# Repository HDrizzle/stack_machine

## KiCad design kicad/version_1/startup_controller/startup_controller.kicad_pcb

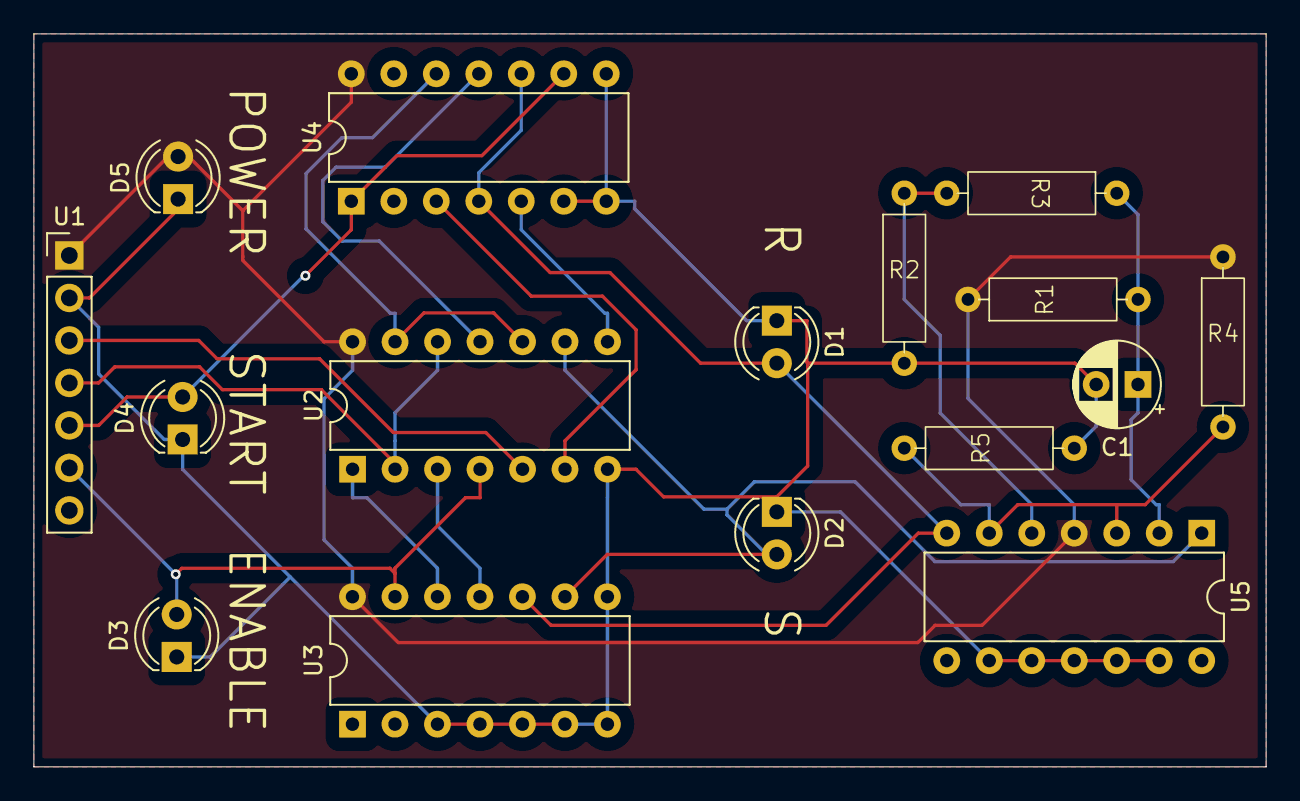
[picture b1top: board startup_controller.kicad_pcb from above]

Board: 2 copper layers, 73.7 x 43.8 mm, 16 parts (0 on the bottom side), 17 nets.

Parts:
C1: C; CP_Radial_D5.0mm_P2.50mm
D1, D2, D3, D4, D5: LED; LED_D4.0mm
R1, R2, R3, R4, R5: R; 0.4_pitch_resistor
U1: PinHeader_1x07_P2.54mm_Vertical
U2, U3, U4, U5: DIP-14_W7.62mm

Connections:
unnamed: D1.2 (A), U3.10 (1RESET), U4.4 (0RESET), U4.10 (1RESET), U5.7 (OUT_2)
unnamed: C1.2, D1.1 (K), D2.1 (K), D3.1 (K), D4.1 (K), D5.1 (K), R2.2, R5.2, U1.2 (GND), U2.7 (GND), U3.3 (0CLK), U3.4 (0RESET), U3.5 (0D), U3.6 (0SET), U3.7 (GND), U3.8 (1SET), U4.6 (0SET), U4.7 (GND), U4.8 (1SET), U5.9 (IN-_3), U5.10 (IN+_3), U5.11 (GND), U5.12 (IN+_4), U5.13 (IN-_4)
unnamed: D2.2 (A), U2.9 (4B), U3.9 (1D), U5.1 (OUT_1)
unnamed: D3.2 (A), U1.6 (ENABLE), U2.4 (2A), U3.13 (1Q)
unnamed: D4.2 (A), U1.5 (START), U4.1 (0Q), U4.9 (1D)
unnamed: D5.2 (A), R1.1, R4.1, U1.1 (V+), U2.14 (V+), U3.14 (V+), U4.14 (V+), U5.4 (V+)
unnamed: U1.3 (A_CLK), U2.5 (2B)
unnamed: U1.4 (B_CLK), U2.2 (1B), U2.12 (3B)
unnamed: U2.1 (1A), U3.12 (1Q3)
unnamed: U2.3 (1Q), U3.11 (1CLK)
unnamed: U2.6 (2Q), U4.3 (0CLK)
unnamed: U2.10 (4A), U2.13 (3A), U4.12 (1Q3)
unnamed: U2.11 (3Q), U4.11 (1CLK)
unnamed: U2.8 (4Q), U4.5 (0D)
unnamed: R4.2, R5.1, U5.3 (IN+_1), U5.6 (IN-_2)
unnamed: R2.1, R3.2, U5.5 (IN+_2)
unnamed: C1.1, R1.2, R3.1, U5.2 (IN-_1)

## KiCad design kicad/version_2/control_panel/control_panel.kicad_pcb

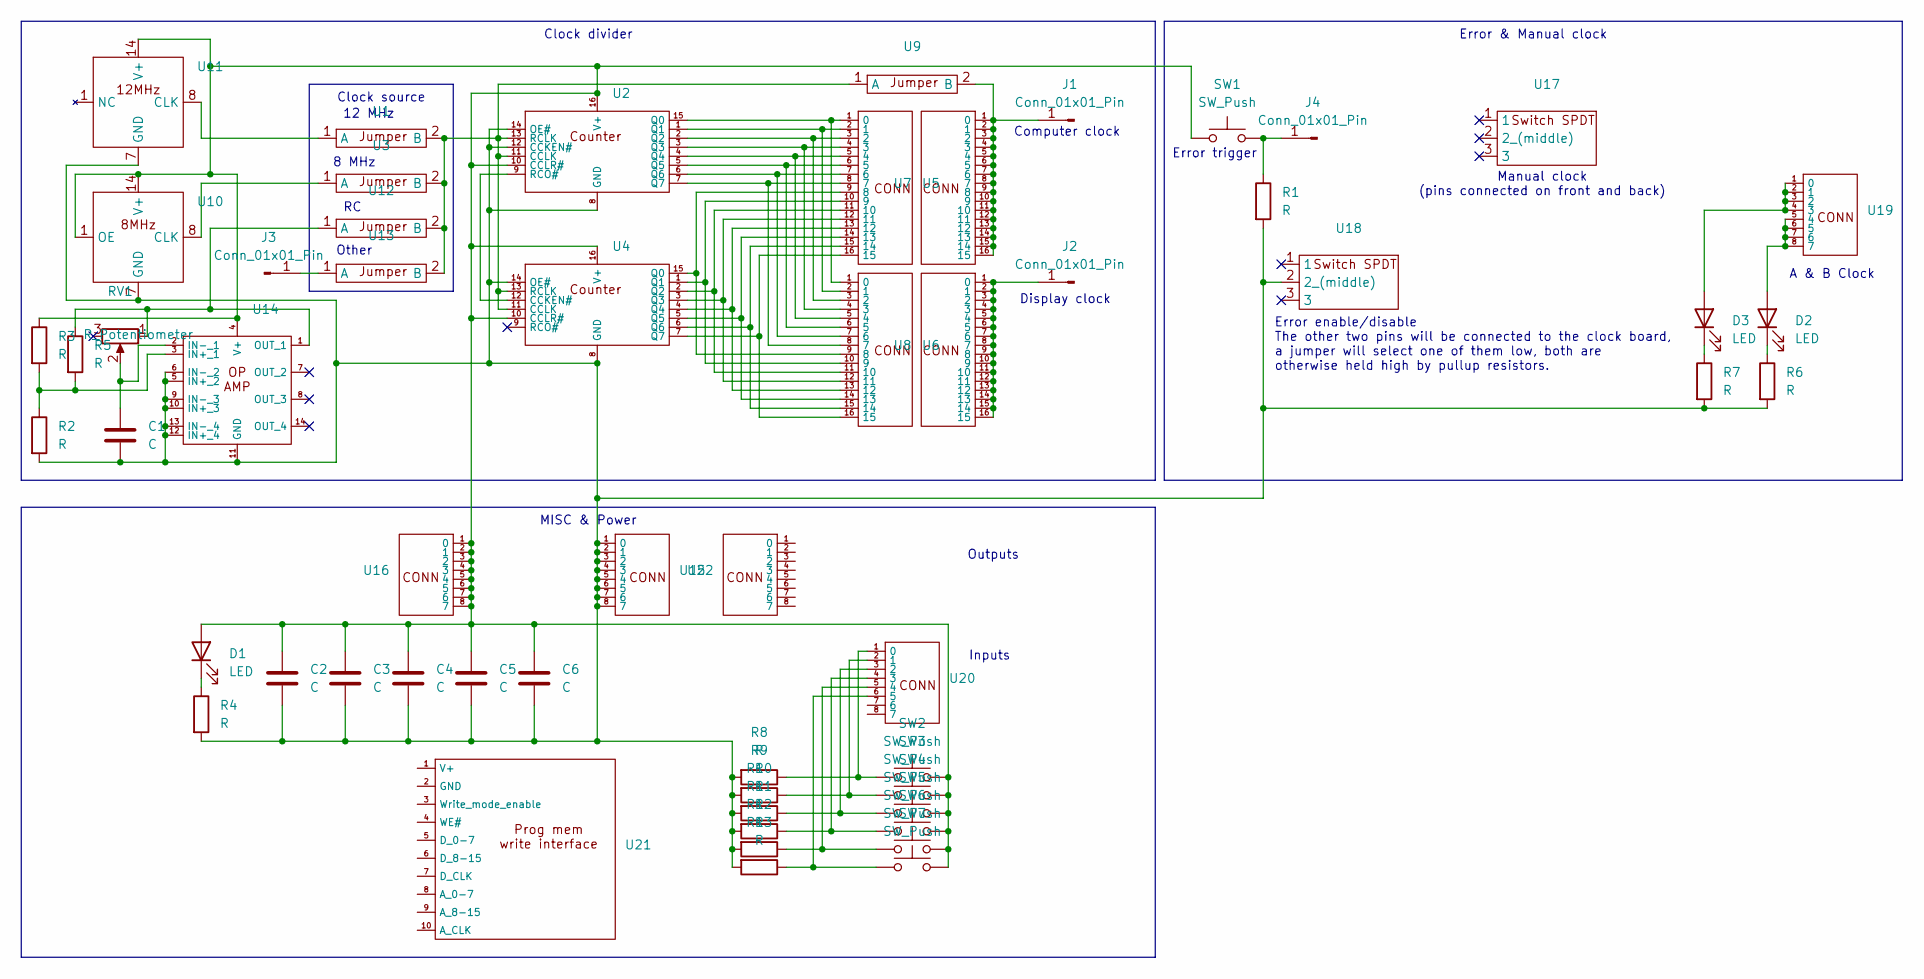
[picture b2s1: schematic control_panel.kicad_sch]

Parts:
C1: C; CP_Radial_D5.0mm_P2.50mm
C2, C3, C4, C5, C6: C; C_Rect_L11.0mm_W4.2mm_P10.00mm_MKT
D1, D2, D3: LED; LED_D3.0mm
J1, J2, J3, J4: Conn_01x01_Pin; PinHeader_1x01_P2.54mm_Vertical
R1, R2, R3, R4, R5, R6, R7, R8, R9, R10, R11, R12, R13: R; 0.4_pitch_resistor
RV1: R_Potentiometer; panel_mount_pot
SW1, SW2, SW3, SW4, SW5, SW6, SW7: SW_Push; SW_PUSH_6mm
U1, U3, U9, U12, U13: PinHeader_1x02_P2.54mm_Vertical
U2, U4: DIP-16_W7.62mm
U5, U6, U7, U8: PinHeader_1x16_P2.54mm_Vertical
U10, U11: crystal_dip_14
U14: DIP-14_W7.62mm
U15, U16, U19, U20, U22: PinHeader_1x08_P2.54mm_Vertical
U17: manual_clock_switch_side
U18: PinHeader_1x03_P2.54mm_Vertical
U21: PinHeader_1x10_P2.54mm_Horizontal

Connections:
unnamed: C2.1, C3.1, C4.1, C5.1, C6.1, D1.2 (A), R3.1, SW1.1, SW2.2, SW3.2, SW4.2, SW5.2, SW6.2, SW7.2, U2.10 (CCLR#), U2.16 (V+), U4.10 (CCLR#), U4.16 (V+), U10.1 (OE), U10.14 (V+), U11.14 (V+), U14.4 (V+), U16.1 (0), U16.2 (1), U16.3 (2), U16.4 (3), U16.5 (4), U16.6 (5), U16.7 (6), U16.8 (7)
unnamed: D1.1 (K), R4.1
unnamed: D2.2 (A), U19.5 (4), U19.6 (5), U19.7 (6), U19.8 (7)
unnamed: D2.1 (K), R6.1
unnamed: D3.2 (A), U19.1 (0), U19.2 (1), U19.3 (2), U19.4 (3)
unnamed: D3.1 (K), R7.1
unnamed: J1.1, U7.1 (0), U7.2 (1), U7.3 (2), U7.4 (3), U7.5 (4), U7.6 (5), U7.7 (6), U7.8 (7), U7.9 (8), U7.10 (9), U7.11 (10), U7.12 (11), U7.13 (12), U7.14 (13), U7.15 (14), U7.16 (15), U9.2 (B)
unnamed: J2.1, U8.1 (0), U8.2 (1), U8.3 (2), U8.4 (3), U8.5 (4), U8.6 (5), U8.7 (6), U8.8 (7), U8.9 (8), U8.10 (9), U8.11 (10), U8.12 (11), U8.13 (12), U8.14 (13), U8.15 (14), U8.16 (15)
unnamed: J3.1, U13.1 (A)
unnamed: J4.1, R1.1, SW1.2
unnamed: U1.1 (A), U11.8 (CLK)
unnamed: U1.2 (B), U2.11 (CCLK), U2.13 (RCLK), U3.2 (B), U4.11 (CCLK), U4.13 (RCLK), U9.1 (A), U12.2 (B), U13.2 (B)
unnamed: U2.15 (Q0), U5.1 (0), U6.1 (0)
unnamed: U2.1 (Q1), U5.2 (1), U6.2 (1)
unnamed: U2.2 (Q2), U5.3 (2), U6.3 (2)
unnamed: U2.3 (Q3), U5.4 (3), U6.4 (3)
unnamed: U2.4 (Q4), U5.5 (4), U6.5 (4)
unnamed: U2.5 (Q5), U5.6 (5), U6.6 (5)
unnamed: U2.6 (Q6), U5.7 (6), U6.7 (6)
unnamed: U2.7 (Q7), U5.8 (7), U6.8 (7)
unnamed: U2.9 (RCO#), U4.12 (CCKEN#)
unnamed: U4.15 (Q0), U5.9 (8), U6.9 (8)
unnamed: U4.1 (Q1), U5.10 (9), U6.10 (9)
unnamed: U4.2 (Q2), U5.11 (10), U6.11 (10)
unnamed: U4.3 (Q3), U5.12 (11), U6.12 (11)
unnamed: U4.4 (Q4), U5.13 (12), U6.13 (12)
unnamed: U4.5 (Q5), U5.14 (13), U6.14 (13)
unnamed: U4.6 (Q6), U5.15 (14), U6.15 (14)
unnamed: U4.7 (Q7), U5.16 (15), U6.16 (15)
unnamed: U3.1 (A), U10.8 (CLK)
unnamed: C1.2, C2.2, C3.2, C4.2, C5.2, C6.2, R1.2, R2.2, R4.2, R6.2, R7.2, R8.2, R9.2, R10.2, R11.2, R12.2, R13.2, U2.8 (GND), U2.12 (CCKEN#), U2.14 (OE#), U4.8 (GND), U4.14 (OE#), U10.7 (GND), U11.7 (GND), U14.5 (IN+_2), U14.6 (IN-_2), U14.9 (IN-_3), U14.10 (IN+_3), U14.11 (GND), U14.12 (IN+_4), U14.13 (IN-_4), U15.1 (0), U15.2 (1), U15.3 (2), U15.4 (3), U15.5 (4), U15.6 (5), U15.7 (6), U15.8 (7), U18.2 (2_(middle))
unnamed: R5.1, RV1.1, U12.1 (A), U14.1 (OUT_1)
unnamed: R2.1, R3.2, R5.2, U14.3 (IN+_1)
unnamed: C1.1, RV1.2, U14.2 (IN-_1)
unnamed: R8.1, SW2.1, U20.1 (0)
unnamed: R9.1, SW3.1, U20.2 (1)
unnamed: R10.1, SW4.1, U20.3 (2)
unnamed: R11.1, SW5.1, U20.4 (3)
unnamed: R12.1, SW6.1, U20.5 (4)
unnamed: R13.1, SW7.1, U20.6 (5)

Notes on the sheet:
Error & Manual clock
MISC & Power
Clock divider
Clock source
Outputs
12 MHz
Error enable/disable The other two pins will be connected to the clock board, a jumper will select one of them low, both are otherwise held high by pullup resistors.
Other
Display clock
Computer clock
8 MHz
Manual clock (pins connected on front and back)
Error trigger
Inputs
A & B Clock

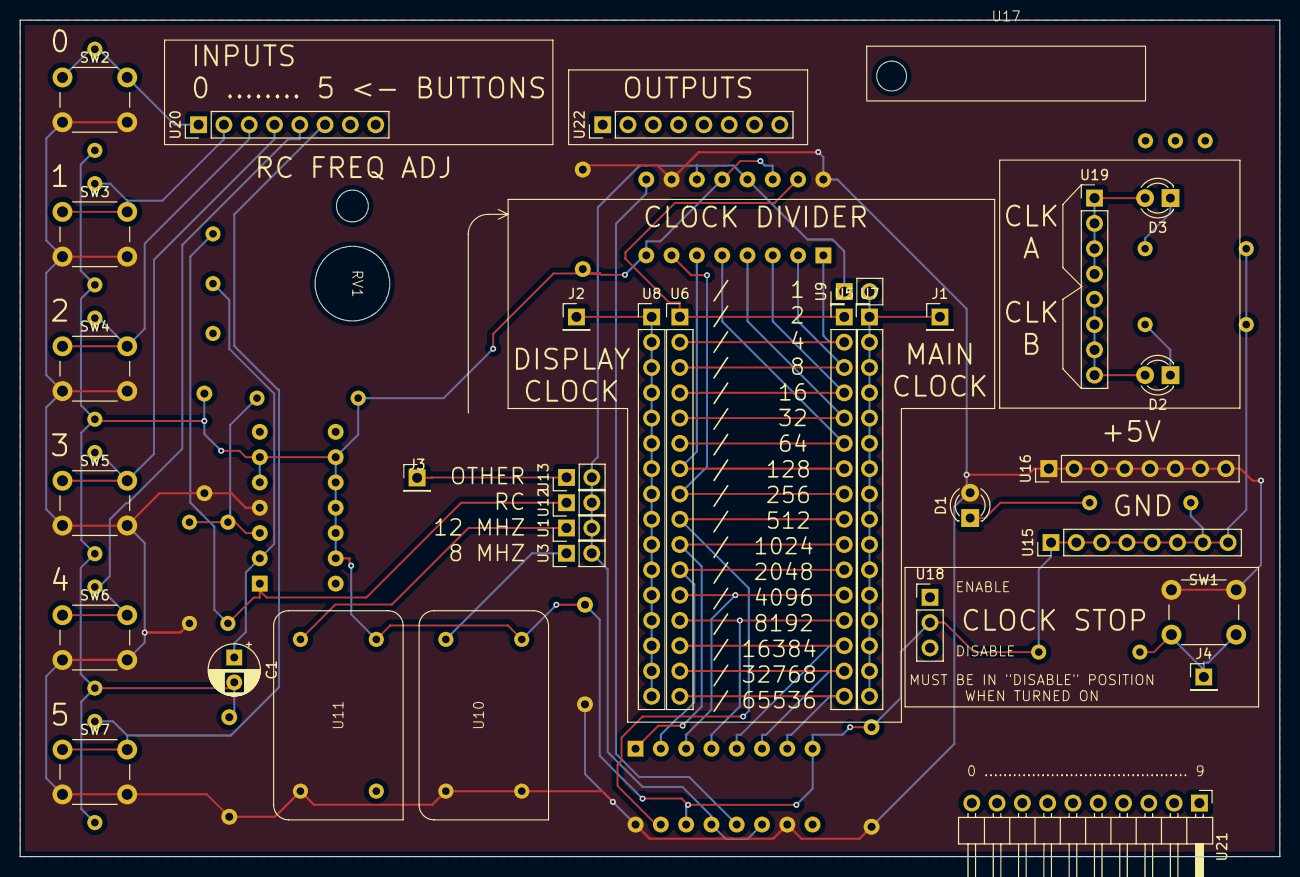
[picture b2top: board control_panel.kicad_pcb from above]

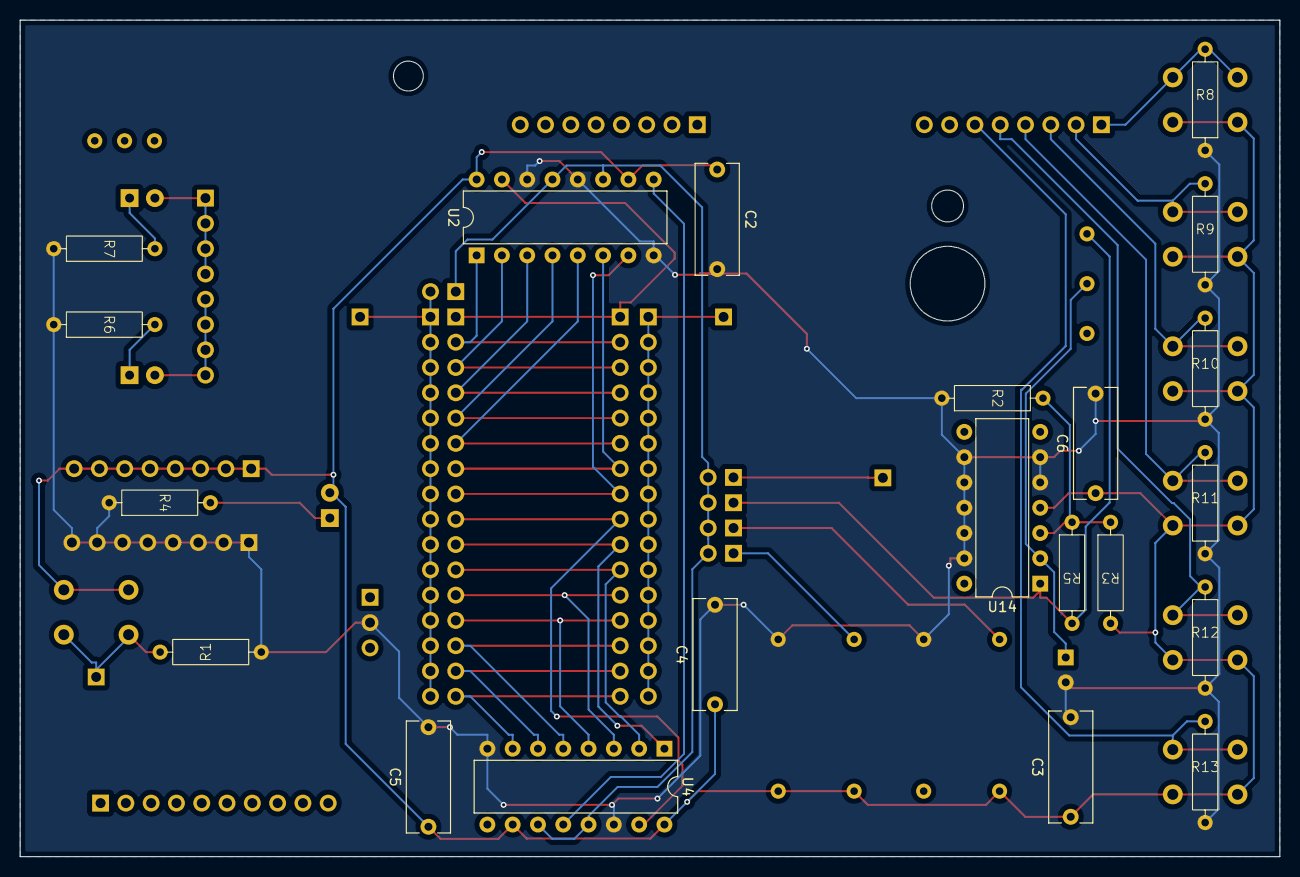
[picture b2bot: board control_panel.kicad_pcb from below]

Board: 2 copper layers, 126.5 x 84.0 mm, 56 parts (21 on the bottom side), 40 nets.

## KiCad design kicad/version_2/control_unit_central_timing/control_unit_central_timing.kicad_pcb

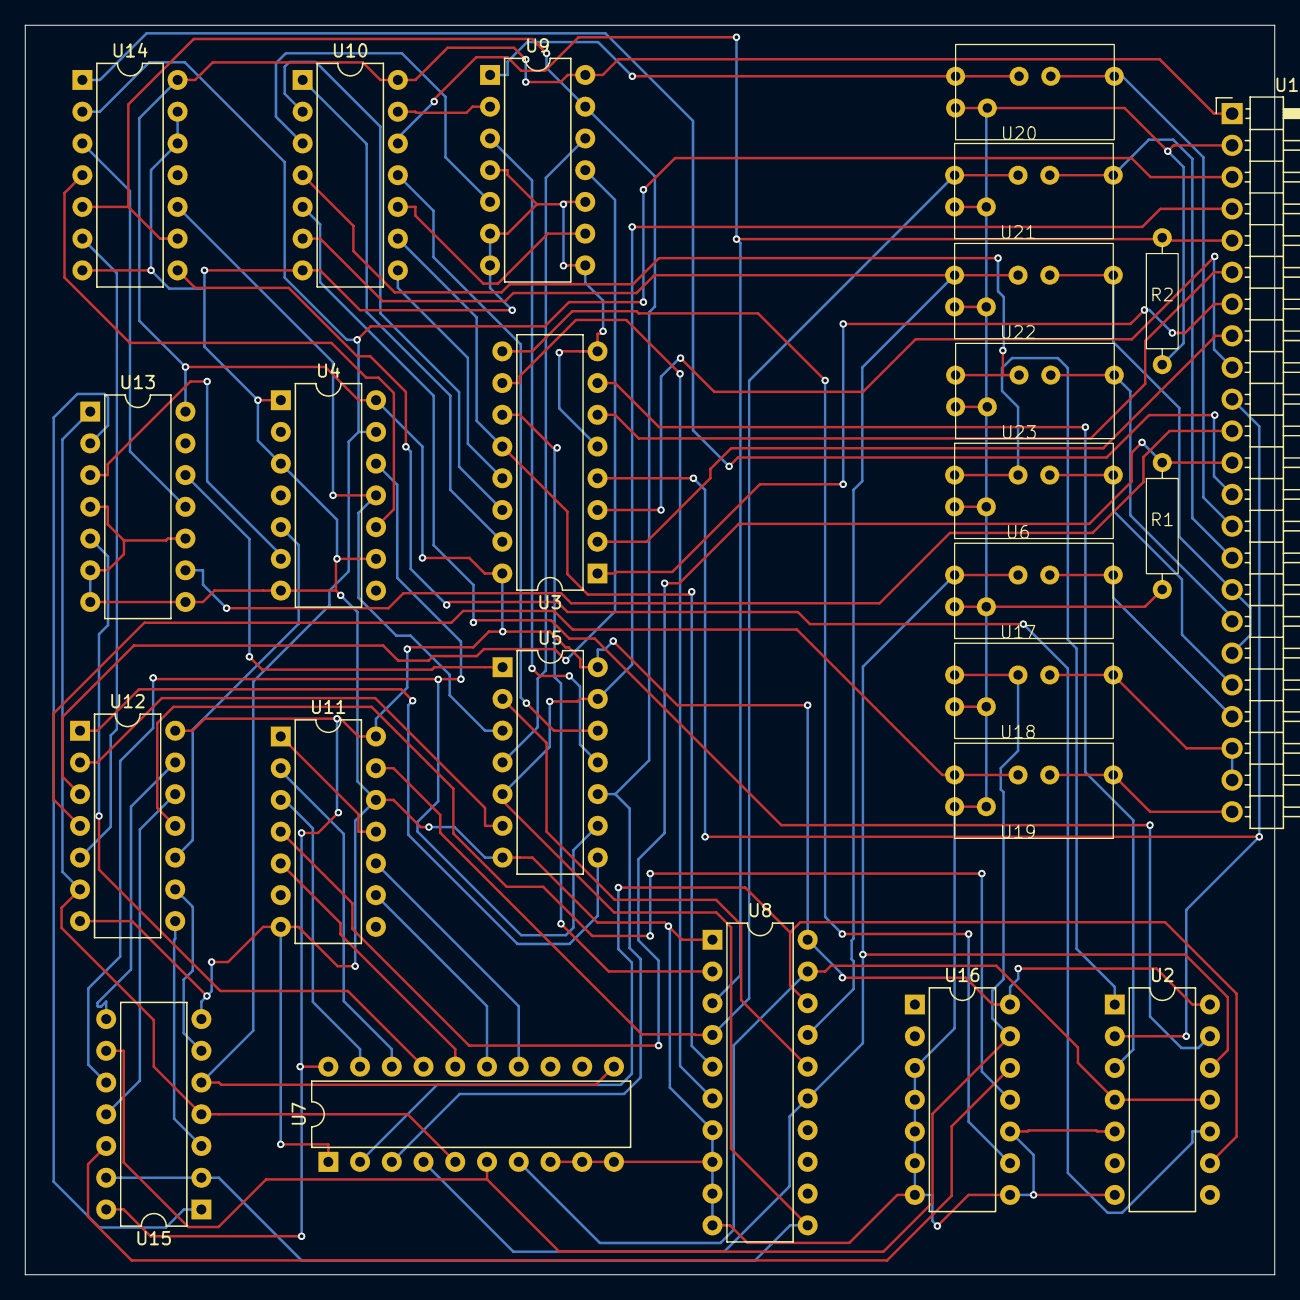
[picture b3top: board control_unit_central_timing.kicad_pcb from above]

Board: 2 copper layers, 100.0 x 100.0 mm, 25 parts (0 on the bottom side), 75 nets.

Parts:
R1, R2: 10k; 0.4_pitch_resistor
U1: PinHeader_1x23_P2.54mm_Horizontal
U2, U4, U5, U9, U10, U11, U12, U13, U14, U15, U16: DIP-14_W7.62mm
U3: DIP-16_W7.62mm
U6, U17, U18, U19, U20, U21, U22, U23: jumper
U7, U8: DIP-20_W7.62mm

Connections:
unnamed: U1.3 (A_CLK), U4.13 (I5), U7.11 (CLK), U14.2 (1B), U15.5 (2B)
unnamed: U1.11 (BUS-0), U13.9 (1D)
unnamed: U1.14 (BUS_MOVE), U20.3 (OUT)
unnamed: R2.1, U1.5 (BUS_MOVE_DONE), U8.3 (D1), U10.12 (3A)
unnamed: U1.13 (BUS_READ_GOTO-DECIDER), U14.1 (1A)
unnamed: U1.4 (B_CLK), U5.5 (2B), U5.13 (3A), U8.11 (CLK), U15.2 (1B), U15.13 (3A)
unnamed: U1.21 (CALL_STACK-POP), U1.22 (CALL_STACK-OE), U18.3 (OUT)
unnamed: U1.20 (CALL_STACK-PUSH), U17.3 (OUT)
unnamed: U1.19 (FAULT), U6.3 (OUT)
unnamed: R1.2, R2.2, U1.2 (GND), U2.5 (A3), U2.7 (GND), U3.5 (E3#), U3.8 (GND), U4.1 (I0), U4.3 (I1), U4.7 (GND), U4.9 (I3), U5.7 (GND), U6.2 (GND), U7.1 (OE#), U7.8 (D6), U7.9 (D7), U7.10 (GND), U8.1 (OE#), U8.7 (D5), U8.8 (D6), U8.9 (D7), U8.10 (GND), U9.4 (0RESET), U9.6 (0SET), U9.7 (GND), U9.8 (1SET), U9.10 (1RESET), U10.7 (GND), U11.7 (GND), U11.12 (B3), U12.7 (GND), U13.4 (0RESET), U13.6 (0SET), U13.7 (GND), U13.8 (1SET), U13.10 (1RESET), U14.7 (GND), U14.12 (3B), U14.13 (3A), U15.7 (GND), U16.3 (0CLK), U16.4 (0RESET), U16.5 (0D), U16.6 (0SET), U16.7 (GND), U16.8 (1SET), U16.10 (1RESET), U17.2 (GND), U18.2 (GND), U19.2 (GND), U20.2 (GND), U21.2 (GND), U22.2 (GND), U23.2 (GND)
unnamed: U1.23 (GOTO_LATCHES_OE), U19.3 (OUT)
unnamed: U1.7 (INSTRUCTION-0), U3.1 (A0)
unnamed: U1.8 (INSTRUCTION-1), U3.2 (A1)
unnamed: U1.9 (INSTRUCTION-2), U3.3 (A2)
unnamed: U1.10 (INSTRUCTION-3), U2.2 (A0), U3.4 (E2#)
unnamed: U1.16 (POST_ADDER_LATCH_CLOCK), U1.18 (PROG_READ), U22.3 (OUT)
unnamed: U1.17 (POST_ADDER_LATCH_OE), U23.3 (OUT)
unnamed: U1.15 (PRE_ADDER_LATCH_CLOCK), U21.3 (OUT)
unnamed: U1.6 (PROG_READ_DONE), U3.6 (E1)
unnamed: R1.1, U1.12 (START), U11.4 (A2)
unnamed: U1.1 (V+), U2.14 (V+), U3.16 (V+), U4.14 (V+), U5.14 (V+), U7.20 (V+), U8.20 (V+), U9.14 (V+), U10.14 (V+), U11.14 (V+), U12.14 (V+), U13.14 (V+), U14.14 (V+), U15.14 (V+), U16.14 (V+)
unnamed: U2.3 (A1), U3.7 (Y7)
unnamed: U2.4 (A2), U2.11 (B2), U7.7 (D5), U8.19 (Q0)
unnamed: U2.9 (B0), U7.2 (D0), U8.18 (Q1)
unnamed: U2.1 (OA), U6.1 (IN)
unnamed: U3.11 (Y4), U8.2 (D0)
unnamed: U3.10 (Y5), U8.6 (D4)
unnamed: U5.2 (1B), U8.16 (Q3)
unnamed: U5.4 (2A), U9.12 (1Q3)
unnamed: U5.11 (3Q), U9.3 (0CLK)
unnamed: U3.15 (Y0), U10.1 (0A)
unnamed: U3.14 (Y1), U10.2 (0B)
unnamed: U2.13 (OB), U10.5 (1A)
unnamed: U8.17 (Q2), U10.6 (1B), U22.1 (IN)
unnamed: U3.13 (Y2), U10.8 (2A)
unnamed: U3.12 (Y3), U8.5 (D3), U10.9 (2B)
unnamed: U9.2 (0Q#), U10.13 (3B)
unnamed: U9.5 (0D), U10.3 (Q0)
unnamed: U10.4 (Q1), U23.1 (IN)
unnamed: U9.9 (1D), U10.10 (Q2)
unnamed: U5.12 (3B), U10.11 (Q3)
unnamed: U7.18 (Q1), U11.2 (A0)
unnamed: U7.19 (Q0), U11.3 (A1)
unnamed: U7.16 (Q3), U11.5 (A3)
unnamed: U7.15 (Q4), U11.9 (B0)
unnamed: U7.14 (Q5), U11.10 (B1)
unnamed: U11.1 (OA), U11.11 (B2)
unnamed: U8.4 (D2), U11.13 (OB), U21.1 (IN)
unnamed: U5.8 (4Q), U12.1 (0A)
unnamed: U5.6 (2Q), U12.2 (0B)
unnamed: U12.5 (1A), U14.6 (2Q)
unnamed: U7.5 (D3), U12.6 (1B), U13.1 (0Q), U15.4 (2A)
unnamed: U12.8 (2A), U15.3 (1Q)
unnamed: U12.9 (2B), U15.6 (2Q)
unnamed: U12.12 (3A), U15.11 (3Q)
unnamed: U12.13 (3B), U15.8 (4Q)
unnamed: U9.11 (1CLK), U12.3 (Q0)
unnamed: U12.4 (Q1), U19.1 (IN)
unnamed: U4.5 (I2), U12.10 (Q2)
unnamed: U12.11 (Q3), U16.11 (1CLK)
unnamed: U4.6 (O2), U13.3 (0CLK)
unnamed: U7.17 (Q2), U13.5 (0D)
unnamed: U13.2 (0Q#), U15.1 (1A)
unnamed: U13.11 (1CLK), U14.3 (1Q)
unnamed: U5.1 (1A), U13.12 (1Q3)
unnamed: U4.10 (O4), U14.4 (2A)
unnamed: U5.10 (4A), U7.3 (D1), U9.13 (1Q), U14.5 (2B), U14.9 (4B)
unnamed: U4.11 (I4), U5.3 (1Q), U14.10 (4A)
unnamed: U2.10 (B1), U14.8 (4Q)
unnamed: U15.12 (3B), U16.12 (1Q3)
unnamed: U4.12 (O5), U5.9 (4B), U15.10 (4A)
unnamed: U7.6 (D4), U15.9 (4B), U16.13 (1Q), U18.1 (IN)
unnamed: U3.9 (Y6), U16.9 (1D)
unnamed: U2.12 (B3), U7.4 (D2), U8.15 (Q4), U17.1 (IN)
unnamed: U9.1 (0Q), U20.1 (IN)

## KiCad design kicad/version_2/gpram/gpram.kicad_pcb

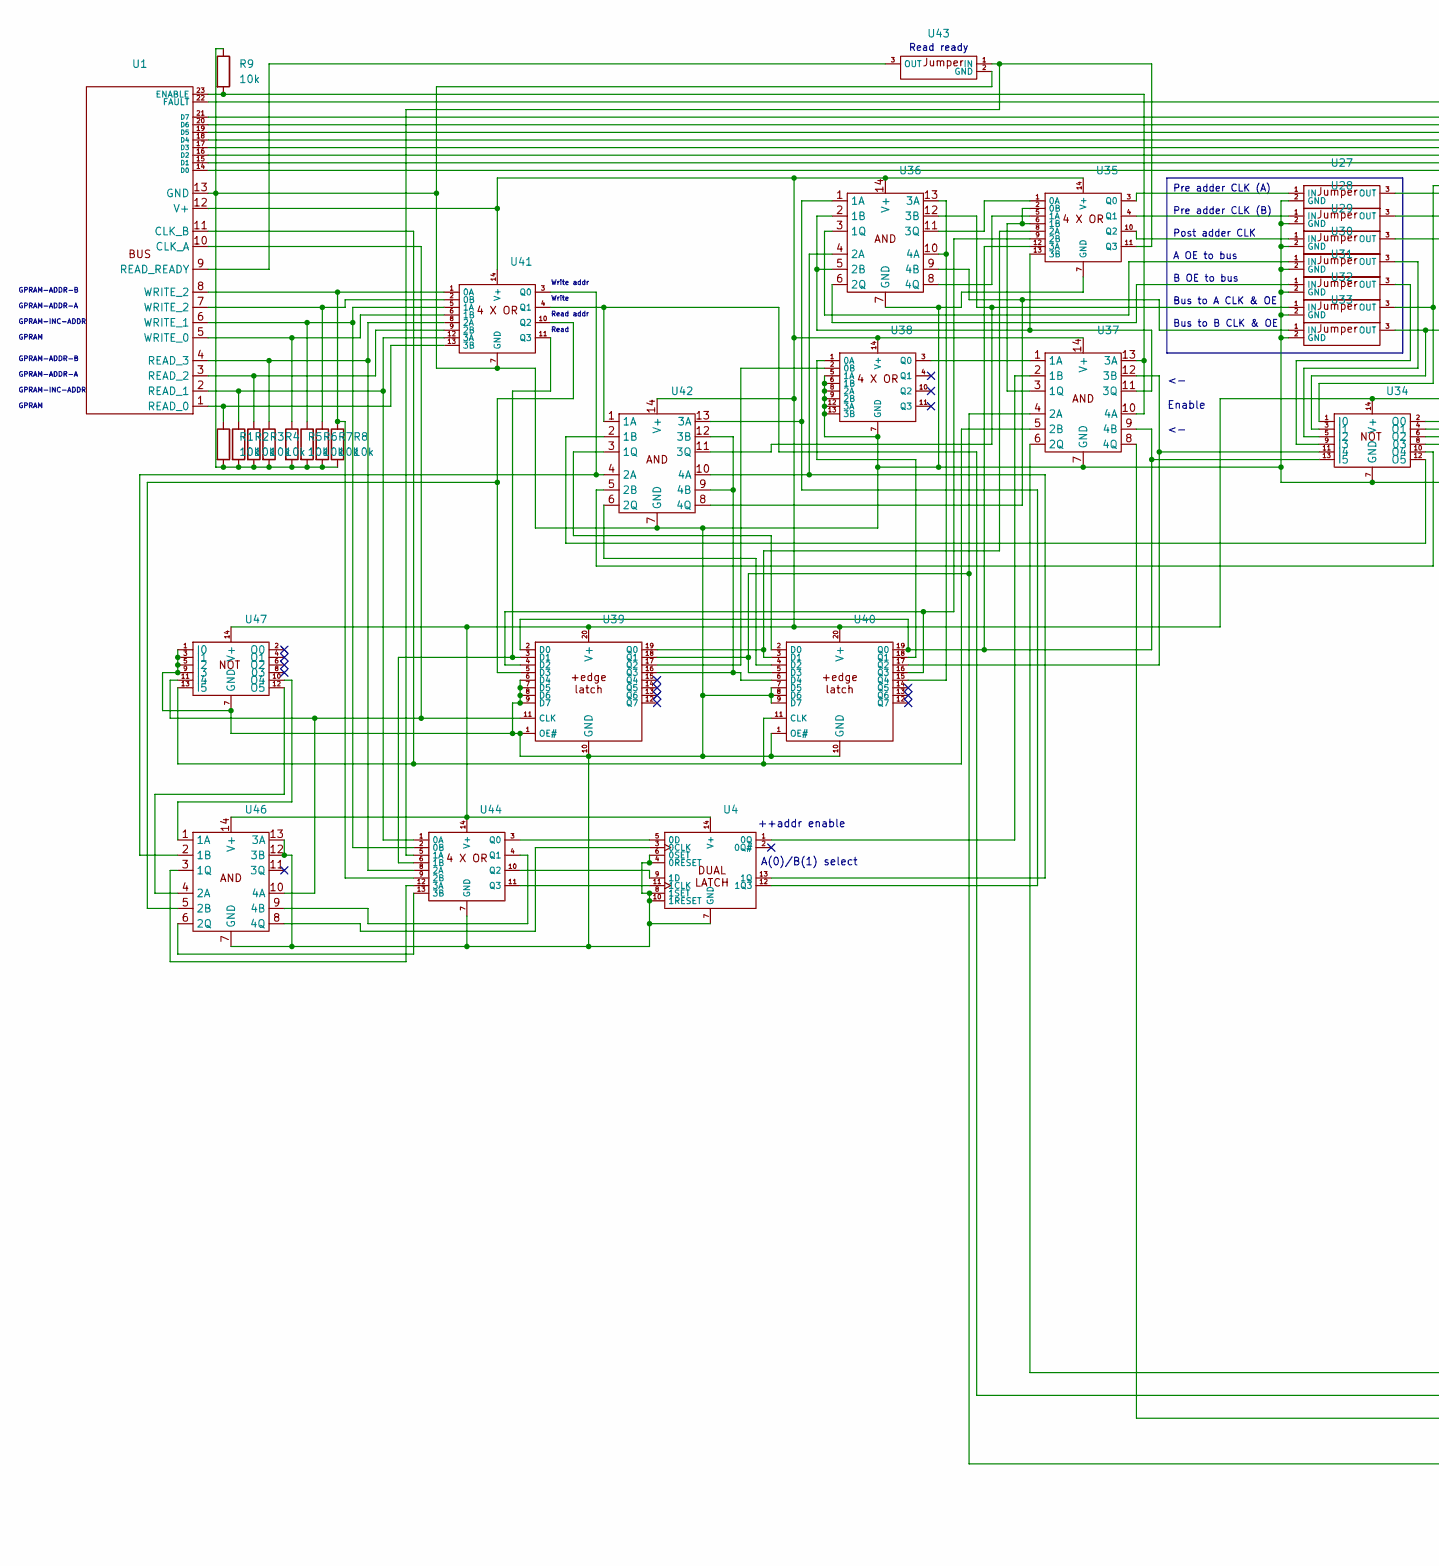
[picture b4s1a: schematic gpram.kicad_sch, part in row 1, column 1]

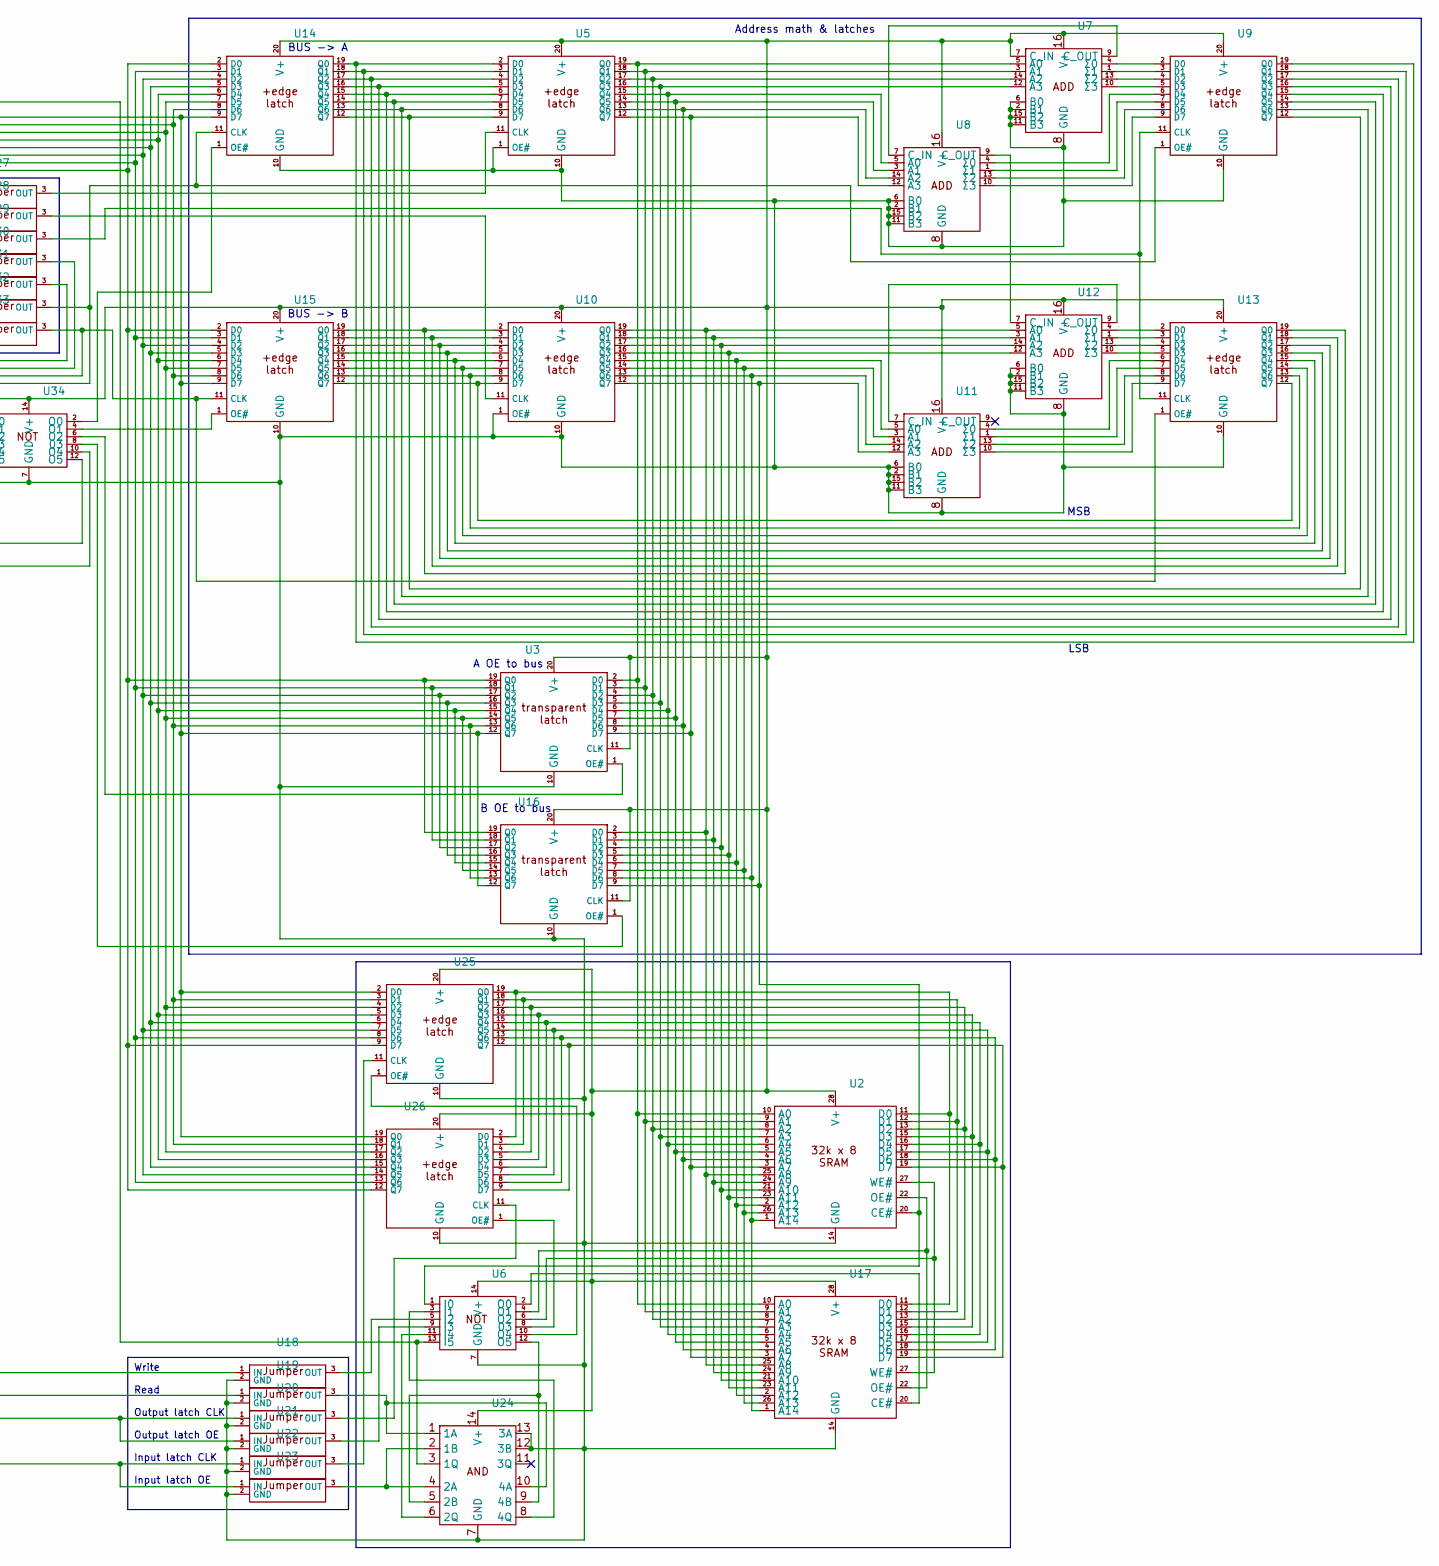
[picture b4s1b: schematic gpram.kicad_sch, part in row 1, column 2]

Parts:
R1, R2, R3, R4, R5, R6, R7, R8, R9: 10k; 0.4_pitch_resistor
U1: PinHeader_1x23_P2.54mm_Vertical
U2, U17: DIP-28_W15.24mm
U3, U5, U9, U10, U13, U14, U15, U16, U25, U26, U39, U40: DIP-20_W7.62mm
U4, U6, U24, U34, U35, U36, U37, U38, U41, U42, U44, U46, U47: DIP-14_W7.62mm
U7, U8, U11, U12: DIP-16_W7.62mm
U18, U19, U20, U21, U22, U23, U27, U28, U29, U30, U31, U32, U33, U43: jumper

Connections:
unnamed: U1.10 (CLK_A), U39.11 (CLK), U46.10 (4A), U47.11 (I4)
unnamed: U1.11 (CLK_B), U37.5 (2B), U40.11 (CLK), U47.13 (I5)
unnamed: U1.14 (D0), U3.19 (Q0), U14.2 (D0), U15.2 (D0), U16.19 (Q0), U25.9 (D7), U26.12 (Q7)
unnamed: U1.15 (D1), U3.18 (Q1), U14.3 (D1), U15.3 (D1), U16.18 (Q1), U25.8 (D6), U26.13 (Q6)
unnamed: U1.16 (D2), U3.17 (Q2), U14.4 (D2), U15.4 (D2), U16.17 (Q2), U25.7 (D5), U26.14 (Q5)
unnamed: U1.17 (D3), U3.16 (Q3), U14.5 (D3), U15.5 (D3), U16.16 (Q3), U25.6 (D4), U26.15 (Q4)
unnamed: U1.18 (D4), U3.15 (Q4), U14.6 (D4), U15.6 (D4), U16.15 (Q4), U25.5 (D3), U26.16 (Q3)
unnamed: U1.19 (D5), U3.14 (Q5), U14.7 (D5), U15.7 (D5), U16.14 (Q5), U25.4 (D2), U26.17 (Q2)
unnamed: U1.20 (D6), U3.13 (Q6), U14.8 (D6), U15.8 (D6), U16.13 (Q6), U25.3 (D1), U26.18 (Q1)
unnamed: U1.21 (D7), U3.12 (Q7), U14.9 (D7), U15.9 (D7), U16.12 (Q7), U25.2 (D0), U26.19 (Q0)
unnamed: R9.2, U1.23 (ENABLE), U37.10 (4A), U37.13 (3A)
unnamed: U1.22 (FAULT), U6.13 (I5), U24.3 (1Q)
unnamed: R1.2, R2.2, R3.2, R4.2, R5.2, R6.2, R7.2, R8.2, R9.1, U1.13 (GND), U2.14 (GND), U3.10 (GND), U4.4 (0RESET), U4.6 (0SET), U4.7 (GND), U4.8 (1SET), U4.10 (1RESET), U5.1 (OE#), U5.10 (GND), U6.7 (GND), U7.2 (B1), U7.6 (B0), U7.8 (GND), U7.11 (B3), U7.15 (B2), U8.2 (B1), U8.6 (B0), U8.8 (GND), U8.11 (B3), U8.15 (B2), U9.10 (GND), U10.1 (OE#), U10.10 (GND), U11.2 (B1), U11.6 (B0), U11.8 (GND), U11.11 (B3), U11.15 (B2), U12.2 (B1), U12.6 (B0), U12.8 (GND), U12.11 (B3), U12.15 (B2), U13.10 (GND), U14.10 (GND), U15.10 (GND), U16.10 (GND), U17.14 (GND), U18.2 (GND), U19.2 (GND), U20.2 (GND), U21.2 (GND), U22.2 (GND), U23.2 (GND), U24.7 (GND), U24.12 (3B), U24.13 (3A), U25.10 (GND), U26.10 (GND), U27.2 (GND), U28.2 (GND), U29.2 (GND), U30.2 (GND), U31.2 (GND), U32.2 (GND), U33.2 (GND), U34.7 (GND), U35.7 (GND), U36.7 (GND), U37.7 (GND), U38.5 (1A), U38.6 (1B), U38.7 (GND), U38.8 (2A), U38.9 (2B), U38.12 (3A), U38.13 (3B), U39.1 (OE#), U39.6 (D4), U39.7 (D5), U39.8 (D6), U39.9 (D7), U39.10 (GND), U40.1 (OE#), U40.7 (D5), U40.8 (D6), U40.9 (D7), U40.10 (GND), U41.7 (GND), U42.7 (GND), U43.2 (GND), U44.7 (GND), U46.7 (GND), U46.12 (3B), U46.13 (3A), U47.1 (I0), U47.3 (I1), U47.5 (I2), U47.7 (GND), U47.9 (I3)
unnamed: R1.1, U1.1 (READ_0), U41.13 (3B)
unnamed: R2.1, U1.2 (READ_1), U41.12 (3A), U44.1 (0A)
unnamed: R3.1, U1.3 (READ_2), U41.9 (2B)
unnamed: R4.1, U1.4 (READ_3), U41.8 (2A), U44.8 (2A)
unnamed: U1.9 (READ_READY), U43.3 (OUT)
unnamed: U1.12 (V+), U2.28 (V+), U3.11 (CLK), U3.20 (V+), U4.14 (V+), U5.20 (V+), U6.14 (V+), U7.7 (C_IN), U7.16 (V+), U8.16 (V+), U9.20 (V+), U10.20 (V+), U11.16 (V+), U12.16 (V+), U13.20 (V+), U14.20 (V+), U15.20 (V+), U16.11 (CLK), U16.20 (V+), U17.28 (V+), U24.14 (V+), U25.20 (V+), U26.20 (V+), U34.14 (V+), U35.14 (V+), U36.14 (V+), U37.14 (V+), U38.14 (V+), U39.20 (V+), U40.20 (V+), U41.14 (V+), U42.14 (V+), U44.14 (V+), U46.14 (V+), U47.14 (V+)
unnamed: R5.1, U1.5 (WRITE_0), U41.6 (1B)
unnamed: R6.1, U1.6 (WRITE_1), U41.5 (1A), U44.2 (0B)
unnamed: U3.1 (OE#), U34.6 (O2)
unnamed: U4.3 (0CLK), U46.8 (4Q)
unnamed: U4.5 (0D), U44.3 (Q0)
unnamed: U4.11 (1CLK), U44.11 (Q3)
unnamed: U4.9 (1D), U44.10 (Q2)
unnamed: U7.9 (C_OUT), U8.7 (C_IN)
unnamed: U7.4 (Σ0), U9.2 (D0)
unnamed: U7.1 (Σ1), U9.3 (D1)
unnamed: U7.13 (Σ2), U9.4 (D2)
unnamed: U7.10 (Σ3), U9.5 (D3)
unnamed: U8.4 (Σ0), U9.6 (D4)
unnamed: U8.1 (Σ1), U9.7 (D5)
unnamed: U8.13 (Σ2), U9.8 (D6)
unnamed: U8.10 (Σ3), U9.9 (D7)
unnamed: U10.11 (CLK), U28.3 (OUT)
unnamed: U10.2 (D0), U13.19 (Q0), U15.19 (Q0)
unnamed: U10.3 (D1), U13.18 (Q1), U15.18 (Q1)
unnamed: U10.4 (D2), U13.17 (Q2), U15.17 (Q2)
unnamed: U10.5 (D3), U13.16 (Q3), U15.16 (Q3)
unnamed: U10.6 (D4), U13.15 (Q4), U15.15 (Q4)
unnamed: U10.7 (D5), U13.14 (Q5), U15.14 (Q5)
unnamed: U10.8 (D6), U13.13 (Q6), U15.13 (Q6)
unnamed: U10.9 (D7), U13.12 (Q7), U15.12 (Q7)
unnamed: U2.25 (A8), U10.19 (Q0), U12.5 (A0), U16.2 (D0), U17.25 (A8)
unnamed: U2.24 (A9), U10.18 (Q1), U12.3 (A1), U16.3 (D1), U17.24 (A9)
unnamed: U2.21 (A10), U10.17 (Q2), U12.14 (A2), U16.4 (D2), U17.21 (A10)
unnamed: U2.23 (A11), U10.16 (Q3), U12.12 (A3), U16.5 (D3), U17.23 (A11)
unnamed: U2.2 (A12), U10.15 (Q4), U11.5 (A0), U16.6 (D4), U17.2 (A12)
unnamed: U2.26 (A13), U10.14 (Q5), U11.3 (A1), U16.7 (D5), U17.26 (A13)
unnamed: U2.1 (A14), U10.13 (Q6), U11.14 (A2), U16.8 (D6), U17.1 (A14)
unnamed: U2.20 (CE#), U6.1 (I0), U10.12 (Q7), U11.12 (A3), U16.9 (D7)
unnamed: U11.7 (C_IN), U12.9 (C_OUT)
unnamed: U11.4 (Σ0), U13.6 (D4)
unnamed: U11.1 (Σ1), U13.7 (D5)
unnamed: U11.13 (Σ2), U13.8 (D6)
unnamed: U11.10 (Σ3), U13.9 (D7)
unnamed: U8.9 (C_OUT), U12.7 (C_IN)
unnamed: U12.4 (Σ0), U13.2 (D0)
unnamed: U12.1 (Σ1), U13.3 (D1)
unnamed: U12.13 (Σ2), U13.4 (D2)
unnamed: U12.10 (Σ3), U13.5 (D3)
unnamed: U9.11 (CLK), U13.11 (CLK), U29.3 (OUT)
unnamed: U13.1 (OE#), U15.11 (CLK), U33.3 (OUT), U34.3 (I1)
unnamed: U9.1 (OE#), U14.11 (CLK), U32.3 (OUT), U34.1 (I0)
unnamed: U14.1 (OE#), U34.2 (O0)
unnamed: U5.2 (D0), U9.19 (Q0), U14.19 (Q0)
unnamed: U5.3 (D1), U9.18 (Q1), U14.18 (Q1)
unnamed: U5.4 (D2), U9.17 (Q2), U14.17 (Q2)
unnamed: U5.5 (D3), U9.16 (Q3), U14.16 (Q3)
unnamed: U5.6 (D4), U9.15 (Q4), U14.15 (Q4)
unnamed: U5.7 (D5), U9.14 (Q5), U14.14 (Q5)
unnamed: U5.8 (D6), U9.13 (Q6), U14.13 (Q6)
unnamed: U5.9 (D7), U9.12 (Q7), U14.12 (Q7)
unnamed: U15.1 (OE#), U34.4 (O1)
unnamed: U16.1 (OE#), U34.8 (03)
unnamed: U2.10 (A0), U3.2 (D0), U5.19 (Q0), U7.5 (A0), U17.10 (A0)
unnamed: U2.9 (A1), U3.3 (D1), U5.18 (Q1), U7.3 (A1), U17.9 (A1)
unnamed: U2.8 (A2), U3.4 (D2), U5.17 (Q2), U7.14 (A2), U17.8 (A2)
unnamed: U2.7 (A3), U3.5 (D3), U5.16 (Q3), U7.12 (A3), U17.7 (A3)
unnamed: U2.6 (A4), U3.6 (D4), U5.15 (Q4), U8.5 (A0), U17.6 (A4)
unnamed: U2.5 (A5), U3.7 (D5), U5.14 (Q5), U8.3 (A1), U17.5 (A5)
unnamed: U2.4 (A6), U3.8 (D6), U5.13 (Q6), U8.14 (A2), U17.4 (A6)
unnamed: U2.3 (A7), U3.9 (D7), U5.12 (Q7), U8.12 (A3), U17.3 (A7)
unnamed: U6.2 (O0), U17.20 (CE#)
unnamed: U2.11 (D0), U17.11 (D0), U25.19 (Q0), U26.2 (D0)
unnamed: U2.12 (D1), U17.12 (D1), U25.18 (Q1), U26.3 (D1)
unnamed: U2.13 (D2), U17.13 (D2), U25.17 (Q2), U26.4 (D2)
unnamed: U2.15 (D3), U17.15 (D3), U25.16 (Q3), U26.5 (D3)
unnamed: U2.16 (D4), U17.16 (D4), U25.15 (Q4), U26.6 (D4)
unnamed: U2.17 (D5), U17.17 (D5), U25.14 (Q5), U26.7 (D5)
unnamed: U2.18 (D6), U17.18 (D6), U25.13 (Q6), U26.8 (D6)
unnamed: U2.19 (D7), U17.19 (D7), U25.12 (Q7), U26.9 (D7)
unnamed: U2.22 (OE#), U6.4 (O1), U17.22 (OE#)
unnamed: U2.27 (WE#), U6.6 (O2), U17.27 (WE#)
unnamed: U18.1 (IN), U37.6 (2Q)
unnamed: U6.5 (I2), U18.3 (OUT)
unnamed: U19.1 (IN), U41.4 (Q1), U42.1 (1A)
unnamed: U19.3 (OUT), U24.1 (1A), U24.10 (4A)
unnamed: U20.1 (IN), U21.1 (IN), U37.8 (4Q)
unnamed: U20.3 (OUT), U26.11 (CLK)
unnamed: U6.9 (I3), U21.3 (OUT)
unnamed: U22.1 (IN), U23.1 (IN), U37.4 (2A), U39.18 (Q1), U40.5 (D3)
unnamed: U22.3 (OUT), U25.11 (CLK)
unnamed: U23.3 (OUT), U24.2 (1B), U24.4 (2A)
unnamed: U6.12 (O5), U24.5 (2B), U24.9 (4B)
unnamed: U6.11 (I4), U24.6 (2Q)
unnamed: U6.3 (I1), U24.8 (4Q)
unnamed: U6.10 (O4), U25.1 (OE#)
unnamed: U6.8 (03), U26.1 (OE#)
unnamed: U27.1 (IN), U35.3 (Q0)
unnamed: U5.11 (CLK), U27.3 (OUT)
unnamed: U28.1 (IN), U35.4 (Q1)
unnamed: U29.1 (IN), U35.10 (Q2)
unnamed: U30.1 (IN), U36.3 (1Q)
unnamed: U30.3 (OUT), U34.5 (I2)
unnamed: U31.1 (IN), U36.6 (2Q)
unnamed: U31.3 (OUT), U34.9 (I3)
unnamed: U32.1 (IN), U36.12 (3B), U42.11 (3Q)
unnamed: U33.1 (IN), U36.9 (4B), U42.8 (4Q)
unnamed: U34.11 (I4), U37.12 (3B), U40.17 (Q2)
unnamed: U34.13 (I5), U35.12 (3A), U37.9 (4B), U39.2 (D0), U40.19 (Q0)
unnamed: U34.10 (O4), U42.5 (2B)
unnamed: U34.12 (O5), U42.2 (1B)
unnamed: U35.1 (0A), U36.11 (3Q)
unnamed: U35.2 (0B), U35.6 (1B), U37.3 (1Q)
unnamed: U35.5 (1A), U36.8 (4Q)
unnamed: U35.8 (2A), U39.19 (Q0), U40.3 (D1)
unnamed: U35.9 (2B), U39.4 (D2), U40.16 (Q3)
unnamed: U35.13 (3B), U36.2 (1B), U36.5 (2B), U37.11 (3Q)
unnamed: U35.11 (Q3), U43.1 (IN), U44.5 (1A)
unnamed: U4.12 (1Q3), U36.1 (1A), U42.13 (3A)
unnamed: U4.13 (1Q), U36.4 (2A), U42.10 (4A)
unnamed: U36.10 (4A), U36.13 (3A), U40.15 (Q4)
unnamed: U37.1 (1A), U38.3 (Q0)
unnamed: U4.1 (0Q), U37.2 (1B)
unnamed: U38.1 (0A), U40.18 (Q1)
unnamed: U38.2 (0B), U39.17 (Q2)
unnamed: U39.3 (D1), U41.11 (Q3), U44.6 (1B)
unnamed: U39.5 (D3), U41.10 (Q2), U46.5 (2B)
unnamed: U39.16 (Q3), U40.6 (D4), U42.9 (4B), U42.12 (3B)
unnamed: U40.2 (D0), U42.3 (1Q)
unnamed: U40.4 (D2), U42.6 (2Q)
unnamed: R8.1, U1.8 (WRITE_2), U41.1 (0A), U44.9 (2B)
unnamed: R7.1, U1.7 (WRITE_2), U41.2 (0B)
unnamed: U41.3 (Q0), U42.4 (2A), U46.2 (1B)
unnamed: U44.12 (3A), U46.3 (1Q)
unnamed: U44.13 (3B), U46.6 (2Q)
unnamed: U44.4 (Q1), U46.9 (4B)
unnamed: U46.1 (1A), U47.10 (O4)
unnamed: U46.4 (2A), U47.12 (O5)

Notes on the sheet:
Pre adder CLK (A) Pre adder CLK (B) Post adder CLK A OE to bus B OE to bus Bus to A CLK & OE Bus to B CLK & OE
Write Read Output latch CLK Output latch OE Input latch CLK Input latch OE
Address math & latches
BUS -> B
Write addr Write Read addr Read
GPRAM-ADDR-B GPRAM-ADDR-A GPRAM-INC-ADDR GPRAM
A(0)/B(1) select
BUS -> A
LSB
<- Enable <-
B OE to bus
++addr enable
MSB
Read ready
A OE to bus
